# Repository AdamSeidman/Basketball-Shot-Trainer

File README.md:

# Basketball Shot Trainer
**Multidisciplinary Senior Design Project for RIT.** &nbsp; _(P21014)_

&ensp;&ensp;The Unified Sports Basketball Shot Trainer analyzes various parameters of a person’s body while shooting a basketball to determine what can be changed to improve the player’s shooting percentage. It analyzes parameters such as arm trajectory, direction of shot, angle of shot, shooting efforts, etc.

&ensp;&ensp;The goals of the project are to design a device that can accomplish the task of analyzing the parameters as described above and correlate them to shooting performance based on court position.  The desired end-result is a working portable, battery-operated prototype with non-intrusive body sensors that can be modeled for production. The device is to be used by Unified Sports to improve the shot accuracy of basketball players. There are no concerns for intellectual property.

&ensp;&ensp;The aim of this project is to provide an approach to developing players' basketball skills through giving the players tangible feedback on their form and shooting performance. Given that our customer is the Special Olympics Unified Sports league, which gives kids with special needs opportunities to grow, a system that provides feedback for improvement can ultimately help them develop better self-confidence in their abilities.

_See our [Confluence Page](https://wiki.rit.edu/pages/viewpage.action?spaceKey=P21014&title=Project+Overview)_  
&nbsp;

### Our Team: 
| **Member**     | **Major**              | **Role**                                          | **Contact**     |
| -------------- | :--------------------: | :-----------------------------------------------: | :-------------: |
| Matthew Fuss   | Electrical Engineering | App Development/Sensor Integration, Documentation | mjf3758@rit.edu |
| Trevor Hess    | Mechanical Engineering | Team Leader, Project Management, CAD              | tdh8765@rit.edu |
| Mercy Chado    | Biomedical Engineering | Systems Engineering, Communication                | mxc2597@rit.edu |
| Kaitlyn Pohler | Electrical Engineering | Purchasing                                        | kap3922@rit.edu |
| Adam Seidman   | Computer Engineering   | Embedded Systems, CAD                             | ajs1551@rit.edu |
| John Bui       | Industrial Engineering | Lean Implementation                               | jcb2832@rit.edu |

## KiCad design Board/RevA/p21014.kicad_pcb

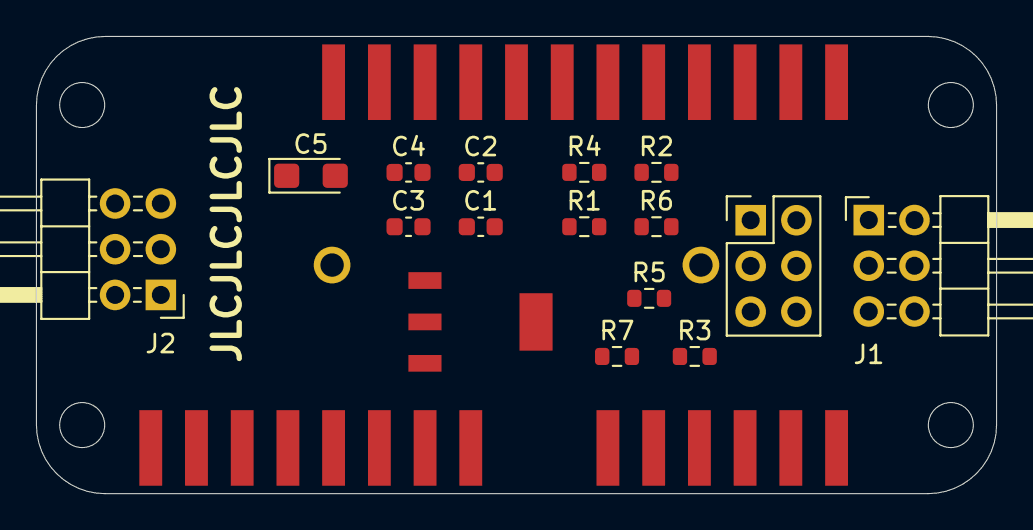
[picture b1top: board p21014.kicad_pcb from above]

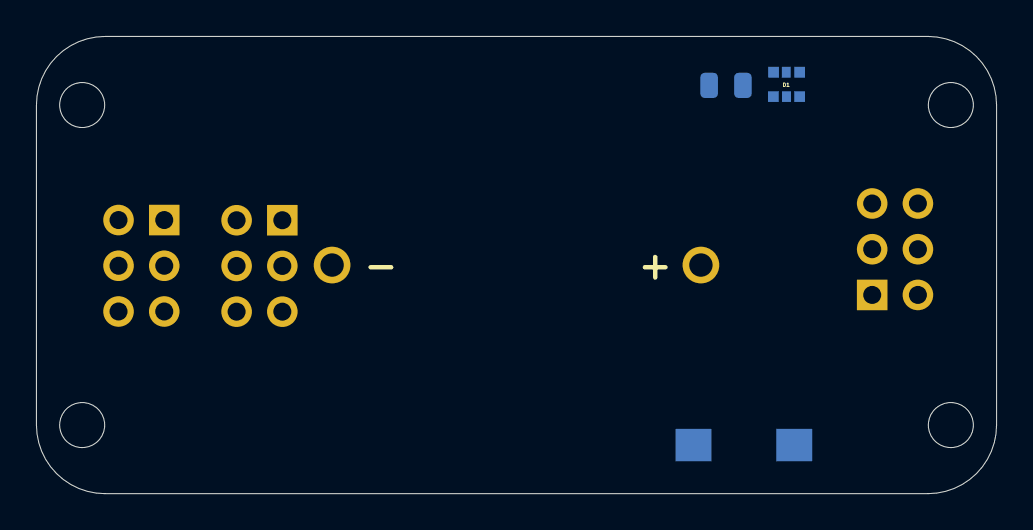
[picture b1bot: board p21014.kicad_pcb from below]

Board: 2 copper layers, 53.3 x 25.4 mm, 27 parts (4 on the bottom side), 20 nets, no tracks yet.

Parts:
BT1: Battery_Cell; AJS-Coin-Cell_1027-Digikey
C1: 0.1uF; C_0603_1608Metric
C2, C3, C4: 1uF; C_0603_1608Metric
C5: 4.7uF_16V; CP_EIA-3216-18_Kemet-A
D1: LED_RGB; RGB_AJS
D2: LED; LED_0805_2012Metric
J1, J2: Conn_01x06_Male; PinHeader_2x03_P2.54mm_Horizontal
J3: Conn_02x03; PinHeader_2x03_P2.54mm_Vertical
J4: Conn_01x08_Female; MSD_8_Pin
J5: Conn_01x12_Female; MSD_12_Pin
J6: Conn_01x06_Female; MSD_6_Pin
MH1, MH2, MH3, MH4: MountingHole_2.5mm
R1, R2, R3, R4: 350; R_0603_1608Metric
R5, R6, R7: 10k; R_0603_1608Metric
SW1: SW_Push; AJS-Switch_CFS-0102TA
VR1: LM1117IMPX-5.0; SOT230P700X180-4N

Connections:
+5V: C2.1, C4.1, C5.1, J1.1, J2.1, J5.1, R5.2, R6.1, VR1.2, VR1.4
+BATT: C1.1, R4.1, SW1.2, VR1.3
/Feather_Board/BLUE: J5.9, R3.1
/Feather_Board/GREEN: J5.8, R1.1
/Feather_Board/RED: J5.7, R2.1
/RST: J1.6, J2.6, J5.5, R7.1
/SCL: J1.4, J2.4, J5.11, R6.2
/SDA: J1.5, J2.5, J5.12, R5.1
GNDREF: BT1.2, C1.2, C2.2, C3.2, C4.2, C5.2, D1.4, D1.5, D1.6, D2.1, J1.3, J2.3, J4.4, J5.2, R7.2, VR1.1
unnamed: BT1.1, SW1.1
unnamed: D1.1, R1.2
unnamed: D1.2, R3.2
unnamed: D1.3, R2.2
unnamed: D2.2, R4.2
unnamed: J3.1, J6.3
unnamed: J3.2, J6.2
unnamed: J3.3, J6.1
unnamed: J3.4, J4.6
unnamed: J3.5, J4.1
unnamed: J3.6, J6.6

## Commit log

2021-09-21 Initial Repo
2021-09-21 Refactor Project for Additional People
2021-09-21 Added Initial Components to RevA Board
2021-09-21 Create placeholder
2021-09-21 Update placeholder
2021-09-21 Restructure Board, Added Sheets and Layout to RevA
2021-09-21 Added Microcontroller Logic to RevA
2021-09-21 Finished Rough RevA and Added Annotations
2021-09-21 Added Footprints to RevA 1/2
2021-09-21 Removed Irrelevant Custom Footprints
2021-09-22 Added Feather Board Project as Reference
2021-09-23 Added \CAD Folder
2021-09-23 created the project directory for some user classes. Also started working on the class structure for the user and players
2021-09-26 Updated Power Pins and Header Layout
2021-09-26 Created Female Pin Header Footprints
2021-09-27 Added Basic PCB Layout
2021-09-27 Added All Proper Footprints to Layout
2021-09-27 Add \CAD\Old STP Files
2021-09-27 Finished Layout RevA Board
    Still needs routing.
2021-09-27 Completely Finished RevA Board
2021-09-27 File Backup Updates
2021-09-27 Updated RevA Parts List/Digikey Order 1
2021-09-28 Added Old .SLDPRT Files
2021-09-28 Uploaded RevB Board Template
    Copied /RevA to /RevB and removed schematic components from .pcbnew (in RevB).
2021-09-28 Updated RevB Schematic
2021-09-28 Roughed out RevB PCB layout
2021-09-30 Finished RevB Layout
2021-09-30 Uploaded Wearable-R0 CAD Files
2021-09-30 Auto-routed RevB
2021-09-30 Created RevB Gerber Files
2021-09-30 Updated RevB/Order 1
    (Digikey)
2021-09-30 Fixed Resources.xlsx, Correct 6 Pin Header
2021-09-30 Updated RevB 3D Models
2021-09-30 Rearranged RevB CAD
2021-09-30 Added Feather M0 Board CAD
2021-09-30 Added Full Assembly of RevB Electronics Construction
2021-09-30 Added /RevC Board
2021-09-30 [ImgBot] Optimize images
    *Total -- 4,026.54kb -> 3,782.51kb (6.06%)
    /CAD/Adafruit BNO055/bottom.jpg -- 97.76kb -> 87.93kb (10.06%)
    /CAD/Adafruit BNO055/top.jpg -- 1,779.22kb -> 1,615.60kb (9.2%)
    /CAD/Adafruit BNO055/Renderings/Render.png -- 1,110.28kb -> 1,071.89kb (3.46%)
    /CAD/Adafruit BNO055/Renderings/Render2.png -- 1,039.28kb -> 1,007.09kb (3.1%)
2021-09-30 Fixed RevC Layout Alignment
2021-10-04 Added Files to Produce RevC Board
2021-10-04 Fixed RevC Outline and STP/DSN
2021-10-04 Updated IMU Mounting Location for RevC
2021-10-04 Create p21014.step
    Part of previous commit.
2021-10-04 Confirmed RevC Mating
2021-10-04 Completed RevC Routing
2021-10-04 Added RevC Gerber Files
2021-10-04 Added cuberotate-app Resource
2021-10-05 Added Working BLE Driver
2021-10-05 Added RevC Initial Code
2021-10-05 Added Connection/Decoding Logic to RevC_1
2021-10-05 Added IMU to RevC_1 Driver
2021-10-05 Finished RevC_1 Driver
2021-10-05 Auto-Format RevC_1.ino
2021-10-05 Fixed Code Flow of RevC_1.ino BLE Startup
2021-10-07 Reorganized .ino File Structure for Arm-Viewer. Also created RevC_2
2021-10-07 Update/Cleanup RevC Code
2021-10-07 Refactored RevC_2 to Look Prettier
2021-10-07 Updated RevC_2 Code for Ease of Use
2021-10-07 Fixed send_data issue with 0s
2021-10-07 Removed Dummy Timing Data
2021-10-08 Update RevC_2.ino
    Refactor.
2021-10-15 Added LED Control to Wearable
2021-10-18 Accidental Footprints
2021-10-19 Added driver for Mercy's testing
2021-10-28 image stuff
2021-10-29 object detection method
2021-10-29 Updated CAD wearable
2021-10-30 added some images to verify that the ball tracking works
2021-11-01 image recognition improvement
2021-11-01 progress made on app development
2021-11-01 Updated RevC_3 to Match Physical Updates
2021-11-01 Updated RevC_Mercy to Match LED Restrictions
2021-11-01 Fixed Missing Blink DEFINE in RevC_3.ino
2021-11-02 Fixed Typo
2021-11-03 app dev
2021-11-07 app development
2021-11-07 app stuff
2021-11-08 fixed the camera
2021-11-09 added menu options to certain app screens
2021-11-09 Update #Resources.xlsx
    Digikey Order 2
2021-11-17 image processing stuff
2021-11-30 not entirely sure
2021-11-30 [ImgBot] Optimize images
    *Total -- 3,530.34kb -> 3,166.09kb (10.32%)
    /Code/Python_Code/two_balls.png -- 183.88kb -> 138.94kb (24.44%)
    /Code/xcode/tutorial project/uitest/uitest/Assets.xcassets/sample.jpg -- 1,636.99kb -> 1,477.90kb (9.72%)
    /Code/xcode/tutorial project/uitest/uitest/Assets.xcassets/sample.imageset/sample.jpg -- 1,636.99kb -> 1,477.90kb (9.72%)
    /Code/Python_Code/image2.png -- 5.11kb -> 4.84kb (5.37%)
    /Code/xcode/MSD2_App/Git Gud/Git Gud/Assets.xcassets/image2.imageset/image2.png -- 5.11kb -> 4.84kb (5.37%)
